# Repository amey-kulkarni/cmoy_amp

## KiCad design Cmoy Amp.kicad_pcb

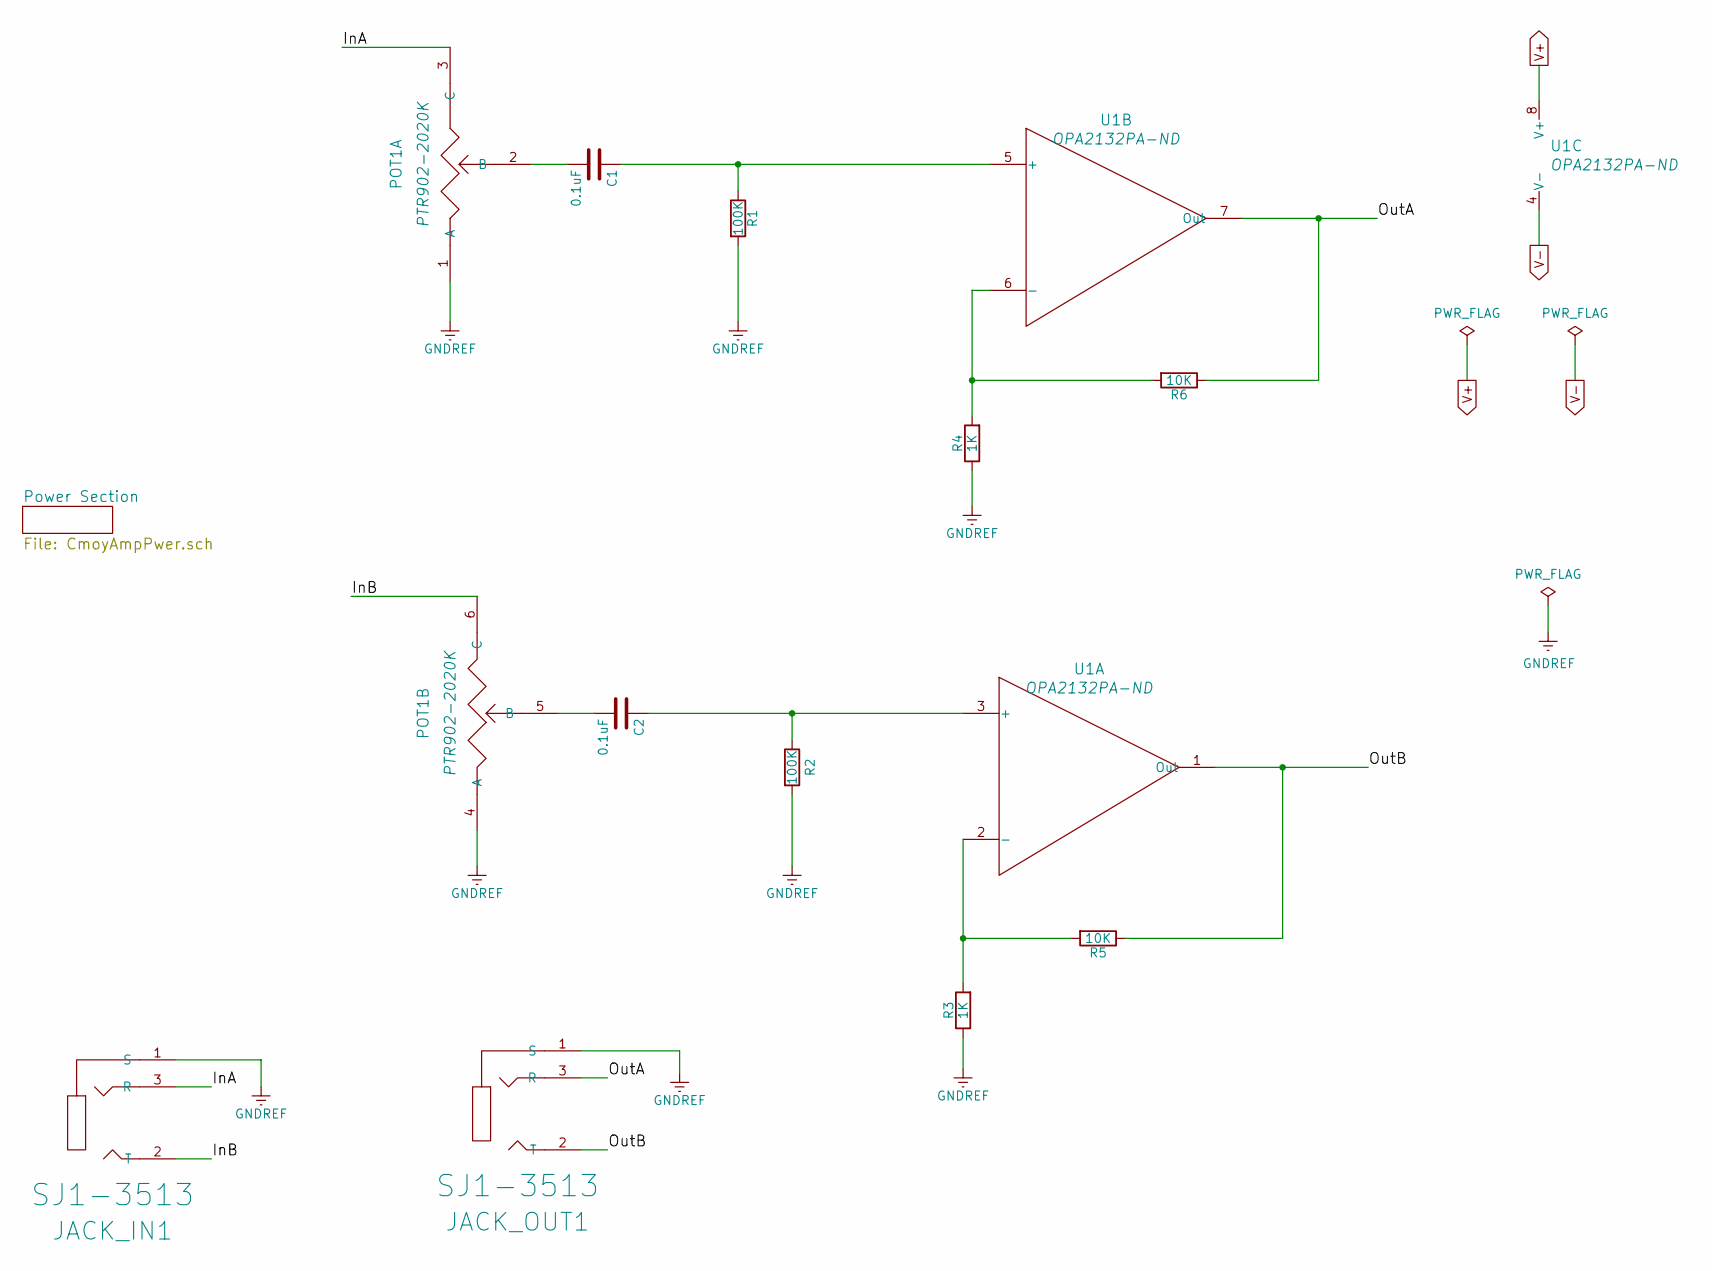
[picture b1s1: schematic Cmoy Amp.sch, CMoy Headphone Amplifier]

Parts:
C1, C2: 0.1uF; C_Rect_L7.2mm_W2.5mm_P5.00mm_FKS2_FKP2_MKS2_MKP2
JACK_IN1: SJ1-3513
JACK_OUT1: SJ1-3513
POT1: PTR902-2020K; Potentiometer_Bourns_PTR902_2020
R1, R2: 100K; R_Axial_DIN0309_L9.0mm_D3.2mm_P12.70mm_Horizontal
R3, R4: 1K; R_Axial_DIN0309_L9.0mm_D3.2mm_P12.70mm_Horizontal
R5, R6: 10K; R_Axial_DIN0309_L9.0mm_D3.2mm_P12.70mm_Horizontal
U1: OPA2132PA-ND; DIP-8_W7.62mm_Socket

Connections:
/InA: JACK_IN1.3 (R), POT1.3 (C)
/InB: JACK_IN1.2 (T), POT1.6 (C)
/OutA: JACK_OUT1.3 (R), R6.1, U1.7 (Out)
/OutB: JACK_OUT1.2 (T), R5.1, U1.1 (Out)
GNDREF: JACK_IN1.1 (S), JACK_OUT1.1 (S), POT1.1 (A), POT1.4 (A), R1.2, R2.2, R3.1, R4.1; also elsewhere on the board
unnamed 5: POT1.7 (A); also elsewhere on the board
unnamed: C1.1, R1.1, U1.5 (+)
unnamed: C1.2, POT1.2 (B)
unnamed: C2.1, R2.1, U1.3 (+)
unnamed: C2.2, POT1.5 (B)
unnamed: R3.2, R5.2, U1.2 (-)
unnamed: R4.2, R6.2, U1.6 (-)
V+: POT1.8 (B), U1.8 (V+); also elsewhere on the board
V-: U1.4 (V-); also elsewhere on the board

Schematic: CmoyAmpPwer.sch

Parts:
BT1: Battery
C3, C4: 220uF
D1: LED_ALT
POT1: PTR902-2020K
R7, R8: 4.7k
RLED1: 10k

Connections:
GNDREF: C3.2, C4.1, R7.2, R8.1; also elsewhere on the board
unnamed: BT1.1, POT1.7 (A)
unnamed: D1.2, RLED1.2
V+: C3.1, POT1.8 (B), R7.1, RLED1.1; also elsewhere on the board
V-: BT1.2, C4.2, D1.1, R8.2; also elsewhere on the board

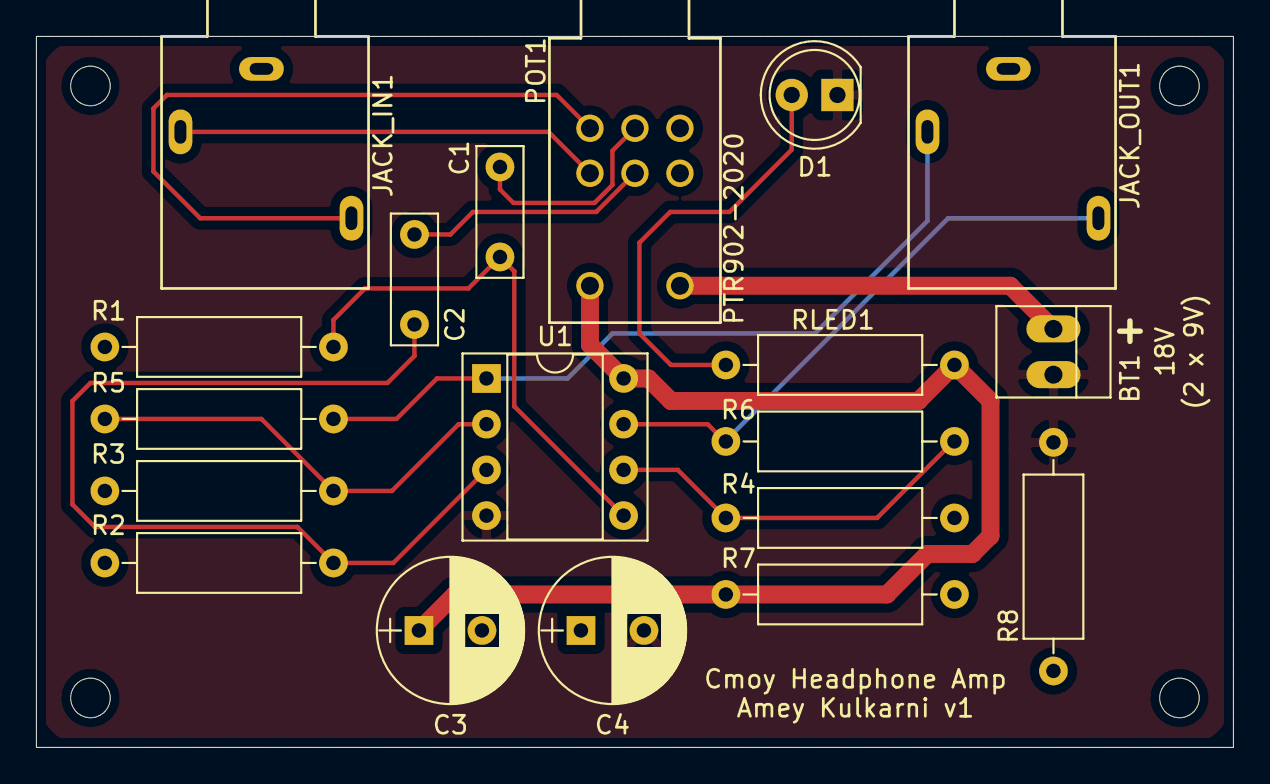
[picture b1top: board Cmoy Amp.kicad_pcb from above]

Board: 2 copper layers, 66.5 x 39.5 mm, 19 parts (0 on the bottom side), 15 nets.

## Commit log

2017-12-07 Set theme jekyll-theme-hacker
2017-12-07 Added local files to repository
2020-08-31 Add PCB layout
    1. Updated OPA2132 footprint: added another unit for power connections
    2. Updated schematic for op-amp footprint update
    3. Added power flags to the schematic
    4. Added potentiometer footprint
    5. Mapped components to footprints
    6. Layed out the PCB
2020-09-01 Reduce PCB size
2020-09-03 Update PCB layout
2020-09-10 Add 3D models
    Added 3D models for the audio jack and the potentiometer-switch
    footprints
    Fixed 3D models for all other components so that the 3D view shows
    all the models
